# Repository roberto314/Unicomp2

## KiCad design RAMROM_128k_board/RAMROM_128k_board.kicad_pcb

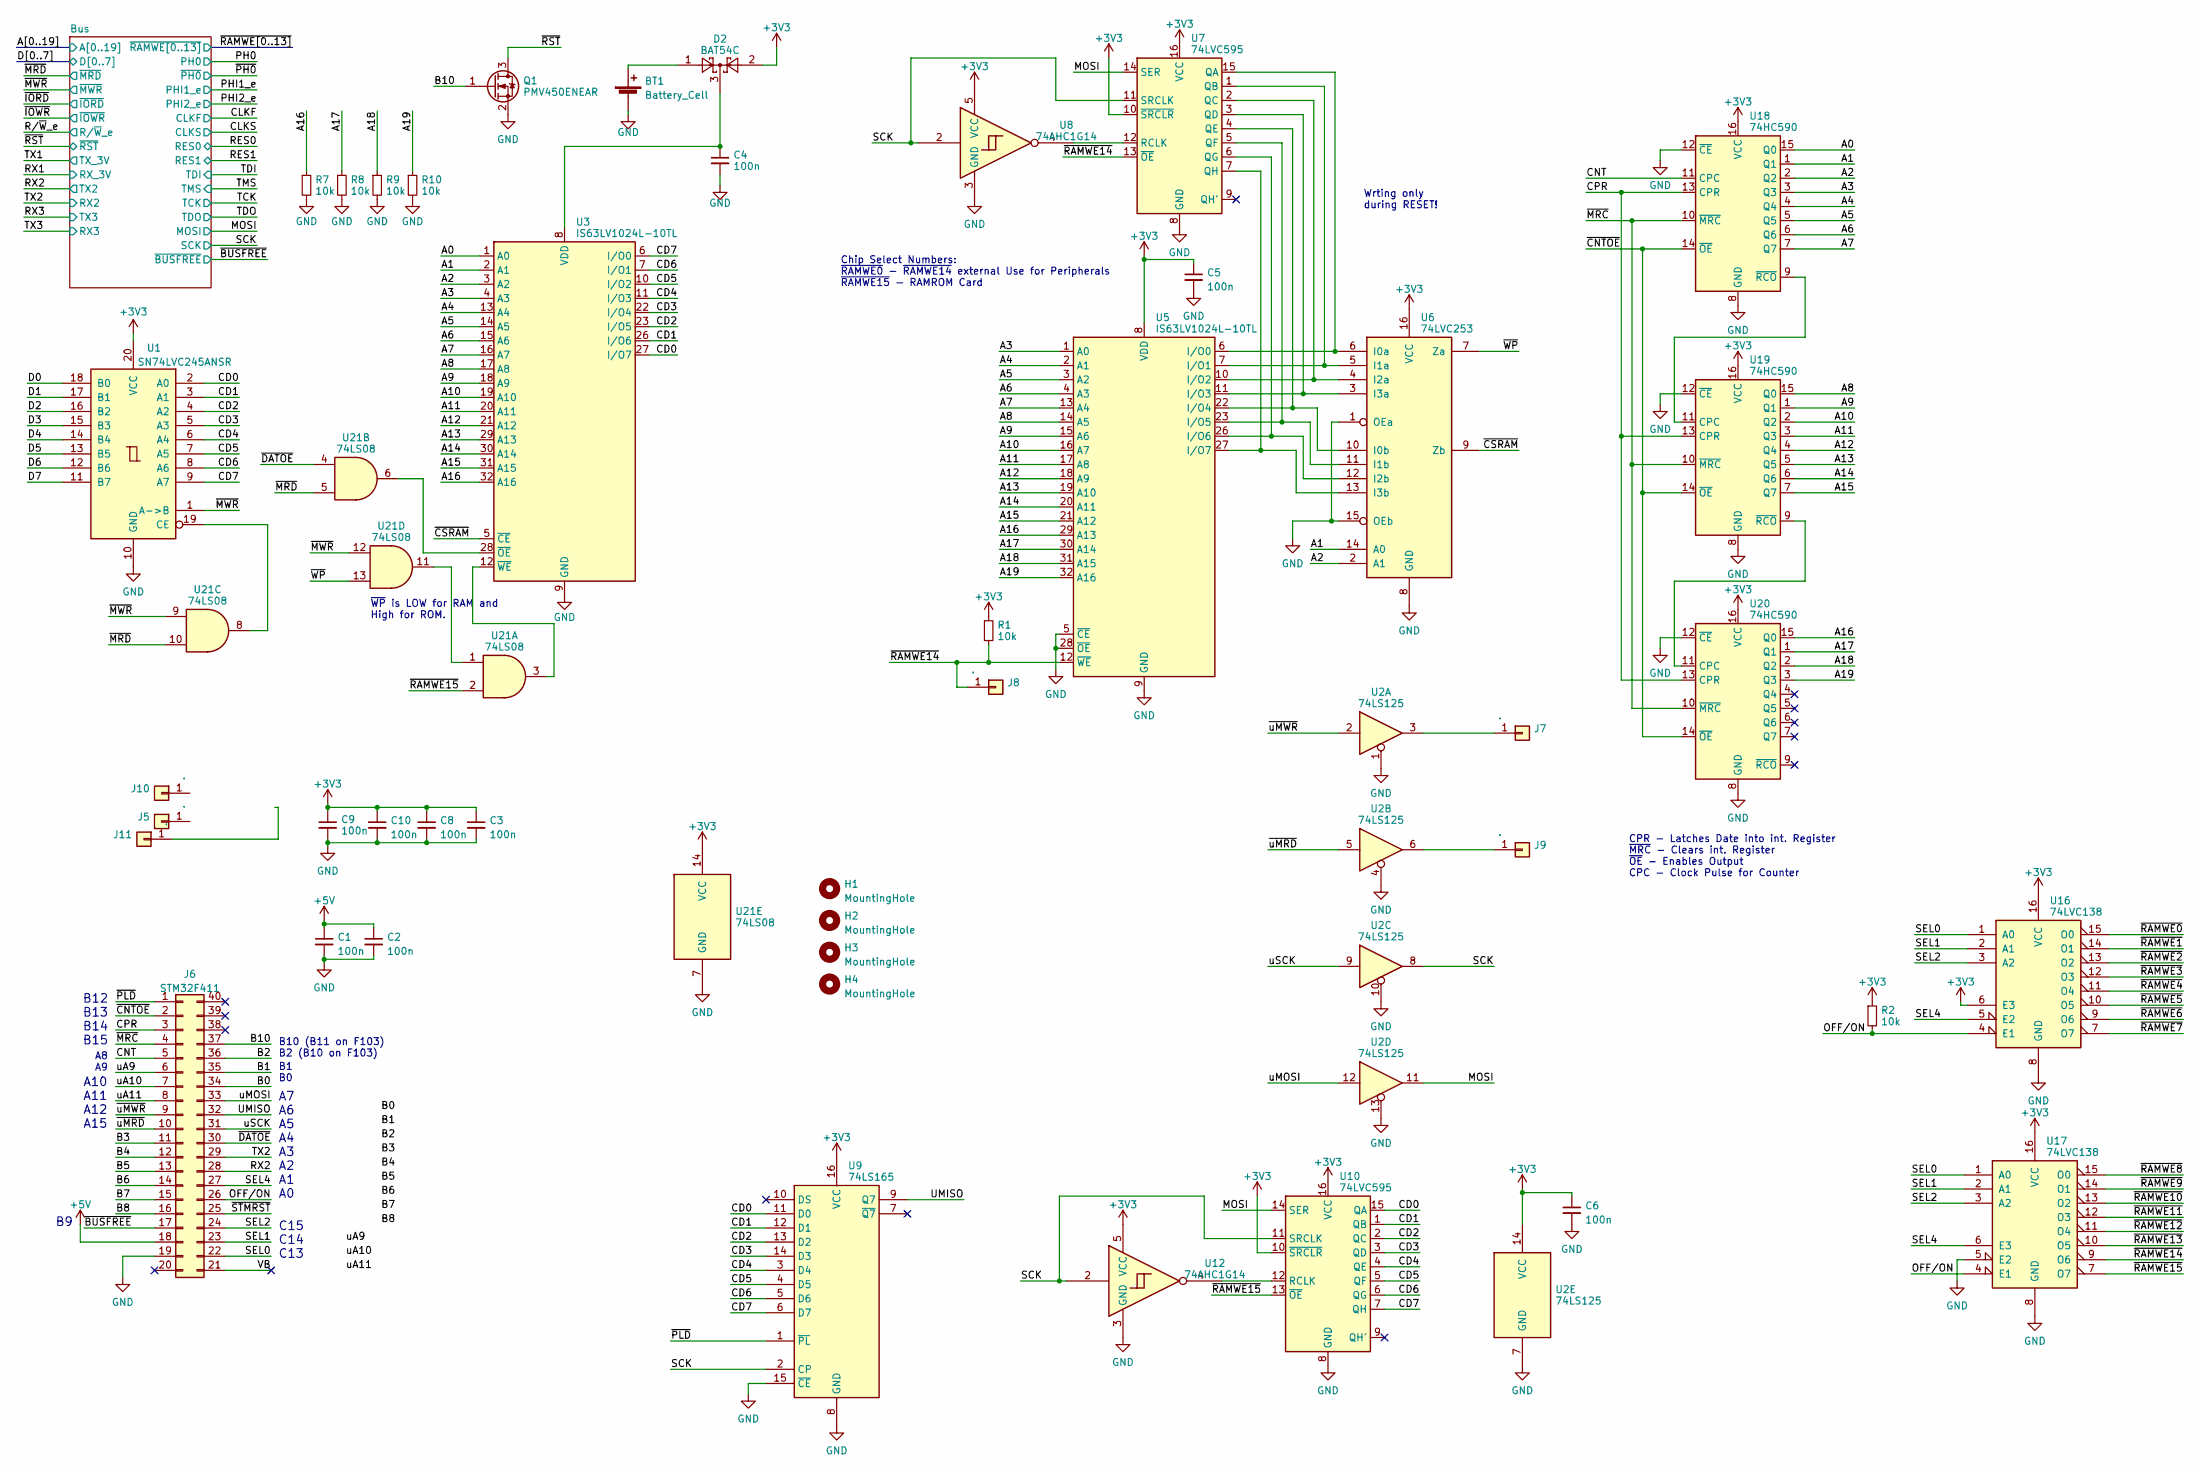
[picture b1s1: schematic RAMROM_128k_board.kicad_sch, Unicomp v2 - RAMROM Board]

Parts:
BT1: Battery_Cell; BatteryHolder_Keystone_103_1x20mm
C1, C2, C3, C4, C5, C6, C8, C9, C10: 100n; C_1206_3216Metric
D2: BAT54C; SOT-23
H1, H2, H3, H4: MountingHole; MountingHole_3.2mm_M3
J5, J7, J8, J9, J10, J11: .; PinHeader_1x01_P2.00mm_Vertical
J6: STM32F411; DIP-40_W15.24mm_Socket_LongPads
Q1: PMV450ENEAR; SOT-23
R1, R2, R7, R8, R9, R10: 10k; R_1206_3216Metric_Pad1.30x1.75mm_HandSolder
U1: SN74LVC245ANSR; SO-20_5.3x12.6mm_P1.27mm
U2: 74LS125; SOIC-14_3.9x8.7mm_P1.27mm
U3, U5: IS63LV1024L-10TL; TSOP-II-32_21.0x10.2mm_P1.27mm
U6: 74LVC253; SO-16_3.9x9.9mm_P1.27mm
U7, U10: 74LVC595; SO-16_3.9x9.9mm_P1.27mm
U8, U12: 74AHC1G14; SOT-23-5
U9: 74LS165; SOIC-16_3.9x9.9mm_P1.27mm
U16, U17: 74LVC138; SOIC-16_3.9x9.9mm_P1.27mm
U18, U19, U20: 74HC590; SOIC-16_3.9x9.9mm_P1.27mm
U21: 74LS08; SOIC-14_3.9x8.7mm_P1.27mm

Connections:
+3V3: C3.1, C5.1, C6.1, C8.1, C9.1, C10.1, D2.2, R1.1, R2.1, U1.20 (VCC), U2.14 (VCC), U5.8 (VDD), U5.24 (VDD), U6.16 (VCC), U7.10 (~SRCLR), U7.16 (VCC), U8.5 (VCC), U9.16 (VCC), U10.10 (~SRCLR), U10.16 (VCC), U12.5 (VCC), U16.6 (E3), U16.16 (VCC), U17.16 (VCC), U18.16 (VCC), U19.16 (VCC), U20.16 (VCC), U21.14 (VCC); also elsewhere on the board
+5V: C1.1, C2.1, J6.18; also elsewhere on the board
/A0: U3.1 (A0), U18.15 (Q0); also elsewhere on the board
/A1: U3.2 (A1), U6.14 (A0), U18.1 (Q1); also elsewhere on the board
/A2: U3.3 (A2), U6.2 (A1), U18.2 (Q2); also elsewhere on the board
/A3: U3.4 (A3), U5.1 (A0), U18.3 (Q3); also elsewhere on the board
/A4: U3.13 (A4), U5.2 (A1), U18.4 (Q4); also elsewhere on the board
/A5: U3.14 (A5), U5.3 (A2), U18.5 (Q5); also elsewhere on the board
/A6: U3.15 (A6), U5.4 (A3), U18.6 (Q6); also elsewhere on the board
/A7: U3.16 (A7), U5.13 (A4), U18.7 (Q7); also elsewhere on the board
/A8: U3.17 (A8), U5.14 (A5), U19.15 (Q0); also elsewhere on the board
/A9: U3.18 (A9), U5.15 (A6), U19.1 (Q1); also elsewhere on the board
/A10: U3.19 (A10), U5.16 (A7), U19.2 (Q2); also elsewhere on the board
/A11: U3.20 (A11), U5.17 (A8), U19.3 (Q3); also elsewhere on the board
/A12: U3.21 (A12), U5.18 (A9), U19.4 (Q4); also elsewhere on the board
/A13: U3.29 (A13), U5.19 (A10), U19.5 (Q5); also elsewhere on the board
/A14: U3.30 (A14), U5.20 (A11), U19.6 (Q6); also elsewhere on the board
/A15: U3.31 (A15), U5.21 (A12), U19.7 (Q7); also elsewhere on the board
/A16: R7.1, U3.32 (A16), U5.29 (A13), U20.15 (Q0); also elsewhere on the board
/A17: R8.1, U5.30 (A14), U20.1 (Q1); also elsewhere on the board
/A18: R9.1, U5.31 (A15), U20.2 (Q2); also elsewhere on the board
/A19: R10.1, U5.32 (A16), U20.3 (Q3); also elsewhere on the board
/B0: J6.34
/B1: J6.35
/B2: J6.36
/B3: J6.11
/B4: J6.12
/B5: J6.13
/B6: J6.14
/B7: J6.15
/B8: J6.16
/B10: J6.37, Q1.1 (G)
/CD0: U1.2 (A0), U3.27 (I/O7), U9.11 (D0), U10.15 (QA)
/CD1: U1.3 (A1), U3.26 (I/O6), U9.12 (D1), U10.1 (QB)
/CD2: U1.4 (A2), U3.23 (I/O5), U9.13 (D2), U10.2 (QC)
/CD3: U1.5 (A3), U3.22 (I/O4), U9.14 (D3), U10.3 (QD)
/CD4: U1.6 (A4), U3.11 (I/O3), U9.3 (D4), U10.4 (QE)
/CD5: U1.7 (A5), U3.10 (I/O2), U9.4 (D5), U10.5 (QF)
/CD6: U1.8 (A6), U3.7 (I/O1), U9.5 (D6), U10.6 (QG)
/CD7: U1.9 (A7), U3.6 (I/O0), U9.6 (D7), U10.7 (QH)
/CNT: J6.5, U18.11 (CPC)
/CPR: J6.3, U18.13 (CPR), U19.13 (CPR), U20.13 (CPR)
/D0: U1.18 (B0); also elsewhere on the board
/D1: U1.17 (B1); also elsewhere on the board
/D2: U1.16 (B2); also elsewhere on the board
/D3: U1.15 (B3); also elsewhere on the board
/D4: U1.14 (B4); also elsewhere on the board
/D5: U1.13 (B5); also elsewhere on the board
/D6: U1.12 (B6); also elsewhere on the board
/D7: U1.11 (B7); also elsewhere on the board
/MOSI: U2.11, U7.14 (SER), U10.14 (SER); also elsewhere on the board
/OFF/ON: J6.26, R2.2, U16.4 (E1), U17.4 (E1)
/RX2: J6.28; also elsewhere on the board
/SCK: U2.8, U7.11 (SRCLK), U8.2, U9.2 (CP), U10.11 (SRCLK), U12.2; also elsewhere on the board
/SEL0: J6.22, U16.1 (A0), U17.1 (A0)
/SEL1: J6.23, U16.2 (A1), U17.2 (A1)
/SEL2: J6.24, U16.3 (A2), U17.3 (A2)
/SEL4: J6.27, U16.5 (E2), U17.6 (E3)
/TX2: J6.29; also elsewhere on the board
/UMISO: J6.32, U9.9 (Q7)
/VB: J6.21
/uA9: J6.6
/uA10: J6.7
/uA11: J6.8
/uMOSI: J6.33, U2.12
/uSCK: J6.31, U2.9
/~BUSFREE: J6.17; also elsewhere on the board
/~CNTOE: J6.2, U18.14 (~OE), U19.14 (~OE), U20.14 (~OE)
/~CSRAM: U3.5 (~CE), U6.9 (Zb)
/~DATOE: J6.30, U21.4
/~MRC: J6.4, U18.10 (~MRC), U19.10 (~MRC), U20.10 (~MRC)
/~MRD: U21.5, U21.10; also elsewhere on the board
/~MWR: U1.1 (A->B), U21.9, U21.12; also elsewhere on the board
/~PLD: J6.1, U9.1 (~PL)
/~RAMWE0: U16.15 (O0); also elsewhere on the board
/~RAMWE1: U16.14 (O1); also elsewhere on the board
/~RAMWE2: U16.13 (O2); also elsewhere on the board
/~RAMWE3: U16.12 (O3); also elsewhere on the board
/~RAMWE4: U16.11 (O4); also elsewhere on the board
/~RAMWE5: U16.10 (O5); also elsewhere on the board
/~RAMWE6: U16.9 (O6); also elsewhere on the board
/~RAMWE7: U16.7 (O7); also elsewhere on the board
/~RAMWE8: U17.15 (O0); also elsewhere on the board
/~RAMWE9: U17.14 (O1); also elsewhere on the board
/~RAMWE10: U17.13 (O2); also elsewhere on the board
/~RAMWE11: U17.12 (O3); also elsewhere on the board
/~RAMWE12: U17.11 (O4); also elsewhere on the board
/~RAMWE13: U17.10 (O5); also elsewhere on the board
/~RAMWE14: J8.1, R1.2, U5.12 (~WE), U7.13 (~OE), U17.9 (O6)
/~RAMWE15: U10.13 (~OE), U17.7 (O7), U21.2
/~RST: Q1.3 (D); also elsewhere on the board
/~STMRST: J6.25
/~WP: U6.7 (Za), U21.13
/~uMRD: J6.10, U2.5
/~uMWR: J6.9, U2.2
GND: BT1.2 (-), C1.2, C2.2, C3.2, C4.2, C5.2, C6.2, C8.2, C9.2, C10.2, J6.19, Q1.2 (S), R7.2, R8.2, R9.2, R10.2, U1.10 (GND), U2.1, U2.4, U2.7 (GND), U2.10, U2.13, U3.9 (GND), U3.25 (GND), U5.5 (~CE), U5.9 (GND), U5.25 (GND), U5.28 (~OE), U6.1 (OEa), U6.8 (GND), U6.15 (OEb), U7.8 (GND), U8.3 (GND), U9.8 (GND), U9.15 (~CE), U10.8 (GND), U12.3 (GND), U16.8 (GND), U17.5 (E2), U17.8 (GND), U18.8 (GND), U18.12 (~CE), U19.8 (GND), U19.12 (~CE), U20.8 (GND), U20.12 (~CE), U21.7 (GND); also elsewhere on the board
unnamed: BT1.1 (+), D2.1
unnamed: C4.1, D2.3, U3.8 (VDD), U3.24 (VDD)
unnamed: J7.1, U2.3
unnamed: J9.1, U2.6
unnamed: U1.19 (CE), U21.8
unnamed: U3.28 (~OE), U21.6
unnamed: U3.12 (~WE), U21.3
unnamed: U5.6 (I/O0), U6.6 (I0a), U7.15 (QA)
unnamed: U5.7 (I/O1), U6.5 (I1a), U7.1 (QB)
unnamed: U5.10 (I/O2), U6.4 (I2a), U7.2 (QC)
unnamed: U5.11 (I/O3), U6.3 (I3a), U7.3 (QD)
unnamed: U5.22 (I/O4), U6.10 (I0b), U7.4 (QE)
unnamed: U5.23 (I/O5), U6.11 (I1b), U7.5 (QF)
unnamed: U5.26 (I/O6), U6.12 (I2b), U7.6 (QG)
unnamed: U5.27 (I/O7), U6.13 (I3b), U7.7 (QH)
unnamed: U7.12 (RCLK), U8.4
unnamed: U10.12 (RCLK), U12.4
unnamed: U18.9 (~RCO), U19.11 (CPC)
unnamed: U19.9 (~RCO), U20.11 (CPC)
unnamed: U21.1, U21.11

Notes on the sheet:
B1 B0
A10 A11 A12 A15
CPR - Latches Date into int. Register ~{MRC} - Clears int. Register ~{OE} - Enables Output CPC - Clock Pulse for Counter
Wrting only during RESET!
A8 A9
B10 (B11 on F103) B2 (B10 on F103)
~{WP} is LOW for RAM and High for ROM.
A7 A6 A5 A4 A3 A2 A1 A0
B12 B13 B14 B15
C15 C14 C13
Chip Select Numbers: ~{RAMWE0} - ~{RAMWE14} external Use for Peripherals ~{RAMWE15} - RAMROM Card

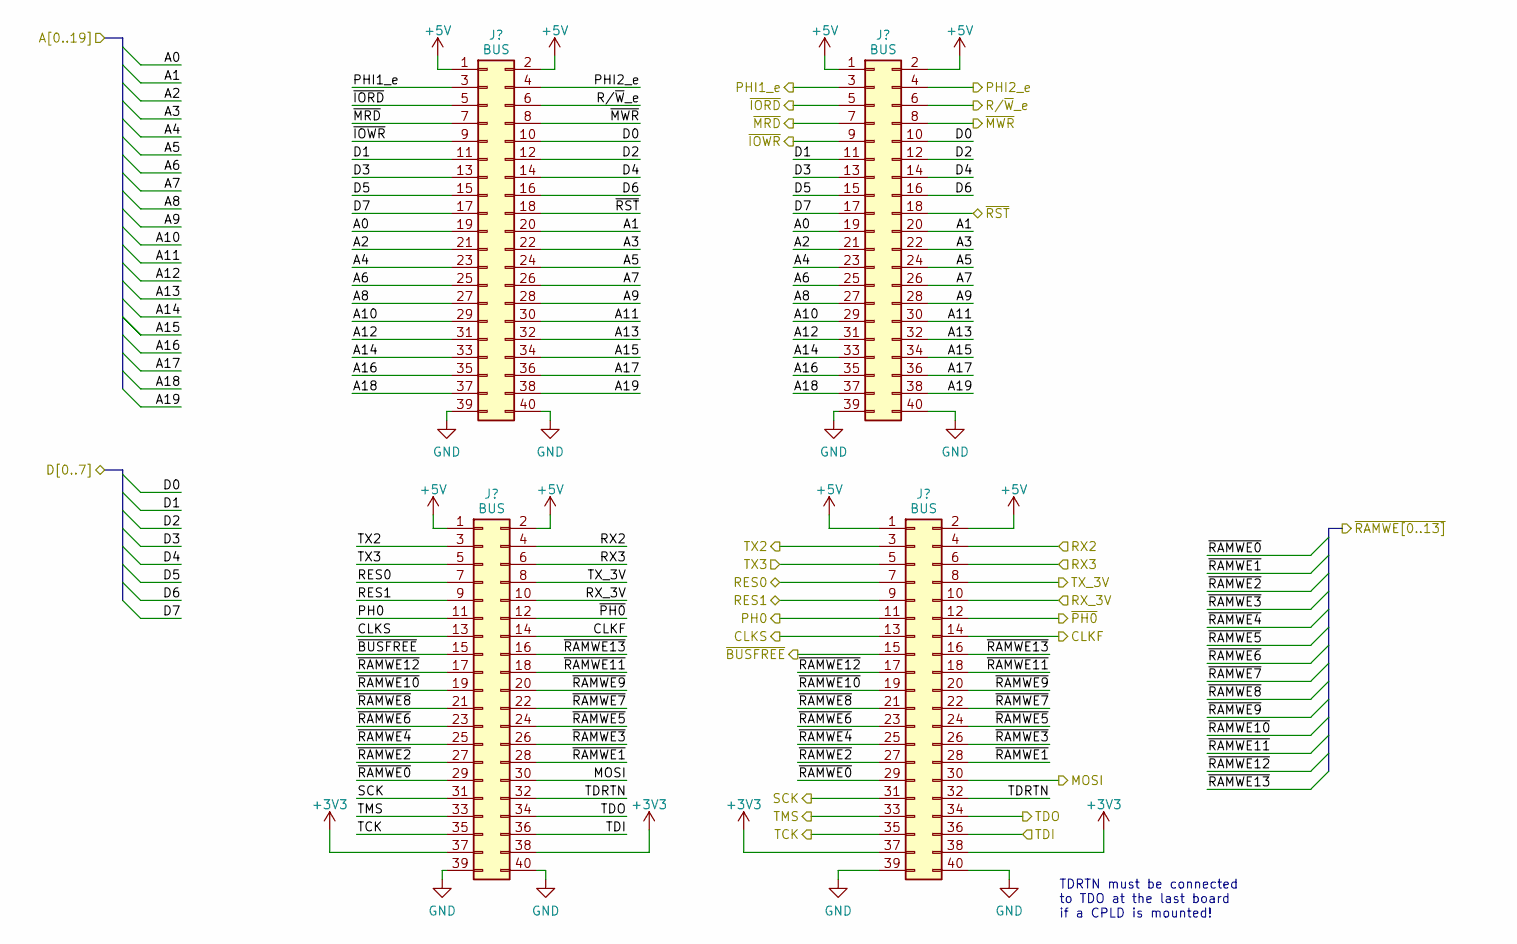
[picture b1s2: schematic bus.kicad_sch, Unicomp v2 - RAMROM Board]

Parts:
J1, J2, J3, J4: BUS; PinSocket_2x20_P2.54mm_Vertical

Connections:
+3V3: J2.37, J2.38, J4.37, J4.38; also elsewhere on the board
+5V: J1.1, J1.2, J2.1, J2.2, J3.1, J3.2, J4.1, J4.2; also elsewhere on the board
/A0: J1.19, J3.19; also elsewhere on the board
/A1: J1.20, J3.20; also elsewhere on the board
/A2: J1.21, J3.21; also elsewhere on the board
/A3: J1.22, J3.22; also elsewhere on the board
/A4: J1.23, J3.23; also elsewhere on the board
/A5: J1.24, J3.24; also elsewhere on the board
/A6: J1.25, J3.25; also elsewhere on the board
/A7: J1.26, J3.26; also elsewhere on the board
/A8: J1.27, J3.27; also elsewhere on the board
/A9: J1.28, J3.28; also elsewhere on the board
/A10: J1.29, J3.29; also elsewhere on the board
/A11: J1.30, J3.30; also elsewhere on the board
/A12: J1.31, J3.31; also elsewhere on the board
/A13: J1.32, J3.32; also elsewhere on the board
/A14: J1.33, J3.33; also elsewhere on the board
/A15: J1.34, J3.34; also elsewhere on the board
/A16: J1.35, J3.35; also elsewhere on the board
/A17: J1.36, J3.36; also elsewhere on the board
/A18: J1.37, J3.37; also elsewhere on the board
/A19: J1.38, J3.38; also elsewhere on the board
/Bus/TDRTN: J2.32, J4.32
/CLKF: J2.14, J4.14
/CLKS: J2.13, J4.13
/D0: J1.10, J3.10; also elsewhere on the board
/D1: J1.11, J3.11; also elsewhere on the board
/D2: J1.12, J3.12; also elsewhere on the board
/D3: J1.13, J3.13; also elsewhere on the board
/D4: J1.14, J3.14; also elsewhere on the board
/D5: J1.15, J3.15; also elsewhere on the board
/D6: J1.16, J3.16; also elsewhere on the board
/D7: J1.17, J3.17; also elsewhere on the board
/MOSI: J2.30, J4.30; also elsewhere on the board
/PH0: J2.11, J4.11
/PHI1_e: J1.3, J3.3
/PHI2_e: J1.4, J3.4
/RES0: J2.7, J4.7
/RES1: J2.9, J4.9
/RX1: J2.10, J4.10
/RX2: J2.3, J4.3; also elsewhere on the board
/RX3: J2.5, J4.5
/R/~W_e: J1.6, J3.6
/SCK: J2.31, J4.31; also elsewhere on the board
/TCK: J2.35, J4.35
/TDI: J2.36, J4.36
/TDO: J2.34, J4.34
/TMS: J2.33, J4.33
/TX1: J2.8, J4.8
/TX2: J2.4, J4.4; also elsewhere on the board
/TX3: J2.6, J4.6
/~BUSFREE: J2.15, J4.15; also elsewhere on the board
/~IORD: J1.5, J3.5
/~IOWR: J1.9, J3.9
/~MRD: J1.7, J3.7; also elsewhere on the board
/~MWR: J1.8, J3.8; also elsewhere on the board
/~PH0: J2.12, J4.12
/~RAMWE0: J2.29, J4.29; also elsewhere on the board
/~RAMWE1: J2.28, J4.28; also elsewhere on the board
/~RAMWE2: J2.27, J4.27; also elsewhere on the board
/~RAMWE3: J2.26, J4.26; also elsewhere on the board
/~RAMWE4: J2.25, J4.25; also elsewhere on the board
/~RAMWE5: J2.24, J4.24; also elsewhere on the board
/~RAMWE6: J2.23, J4.23; also elsewhere on the board
/~RAMWE7: J2.22, J4.22; also elsewhere on the board
/~RAMWE8: J2.21, J4.21; also elsewhere on the board
/~RAMWE9: J2.20, J4.20; also elsewhere on the board
/~RAMWE10: J2.19, J4.19; also elsewhere on the board
/~RAMWE11: J2.18, J4.18; also elsewhere on the board
/~RAMWE12: J2.17, J4.17; also elsewhere on the board
/~RAMWE13: J2.16, J4.16; also elsewhere on the board
/~RST: J1.18, J3.18; also elsewhere on the board
GND: J1.39, J1.40, J2.39, J2.40, J3.39, J3.40, J4.39, J4.40; also elsewhere on the board

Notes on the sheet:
TDRTN must be connected to TDO at the last board if a CPLD is mounted!

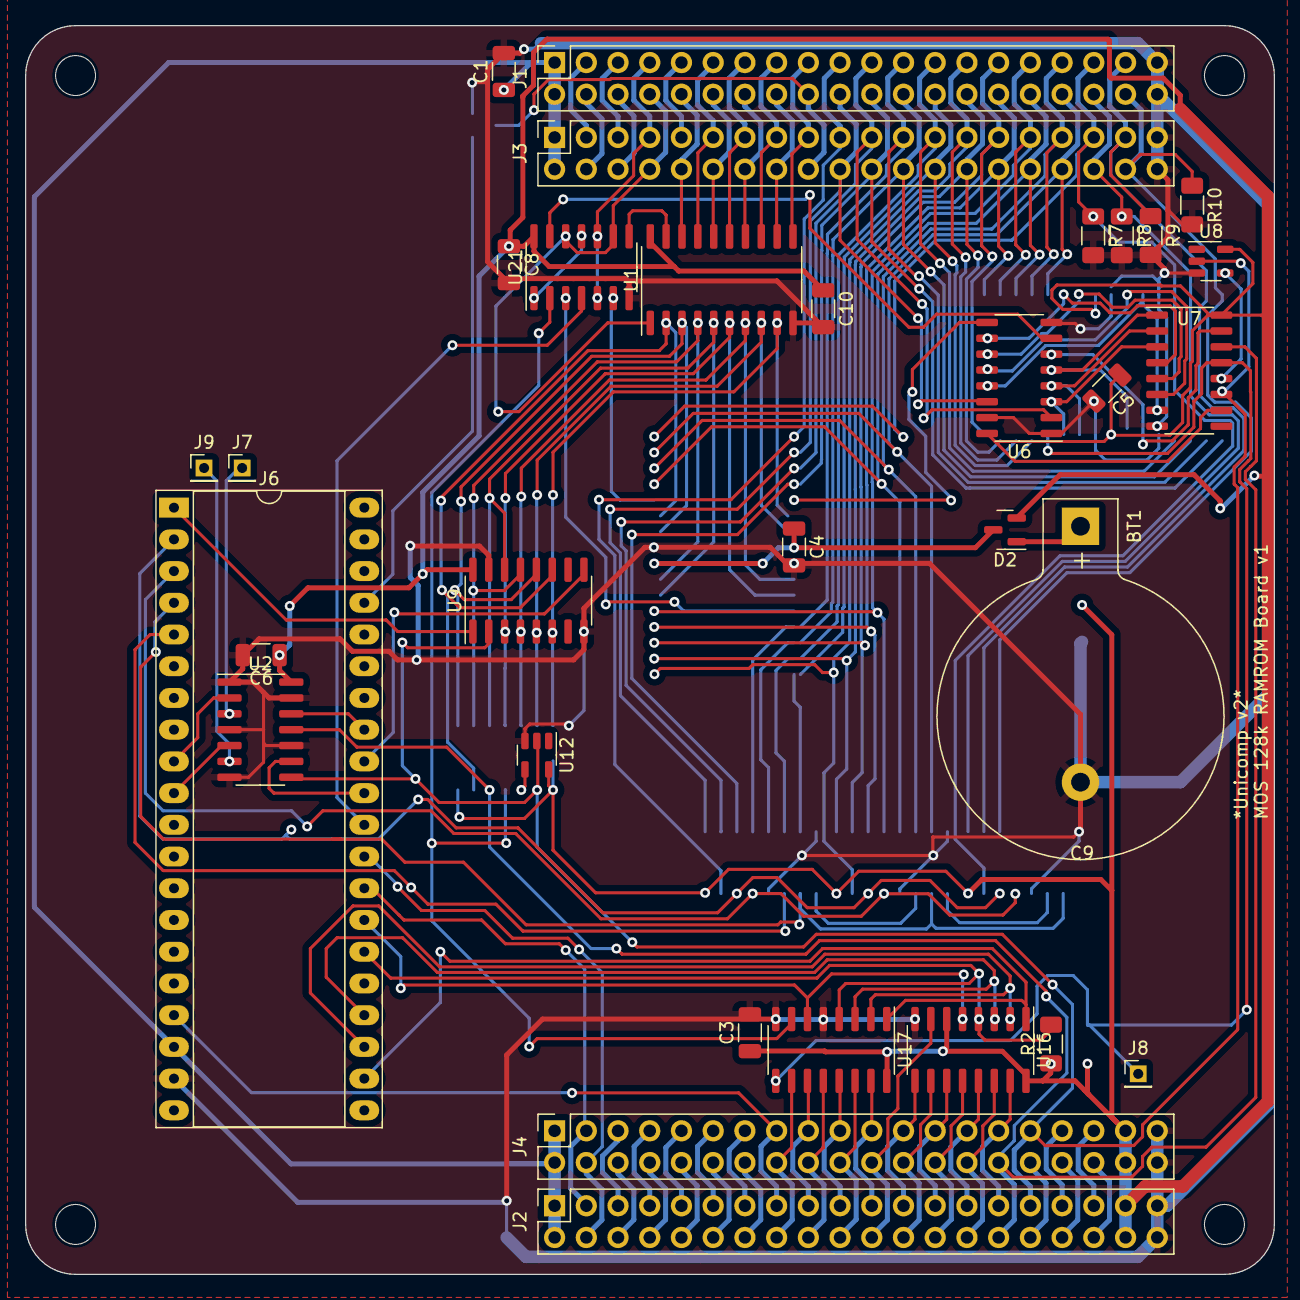
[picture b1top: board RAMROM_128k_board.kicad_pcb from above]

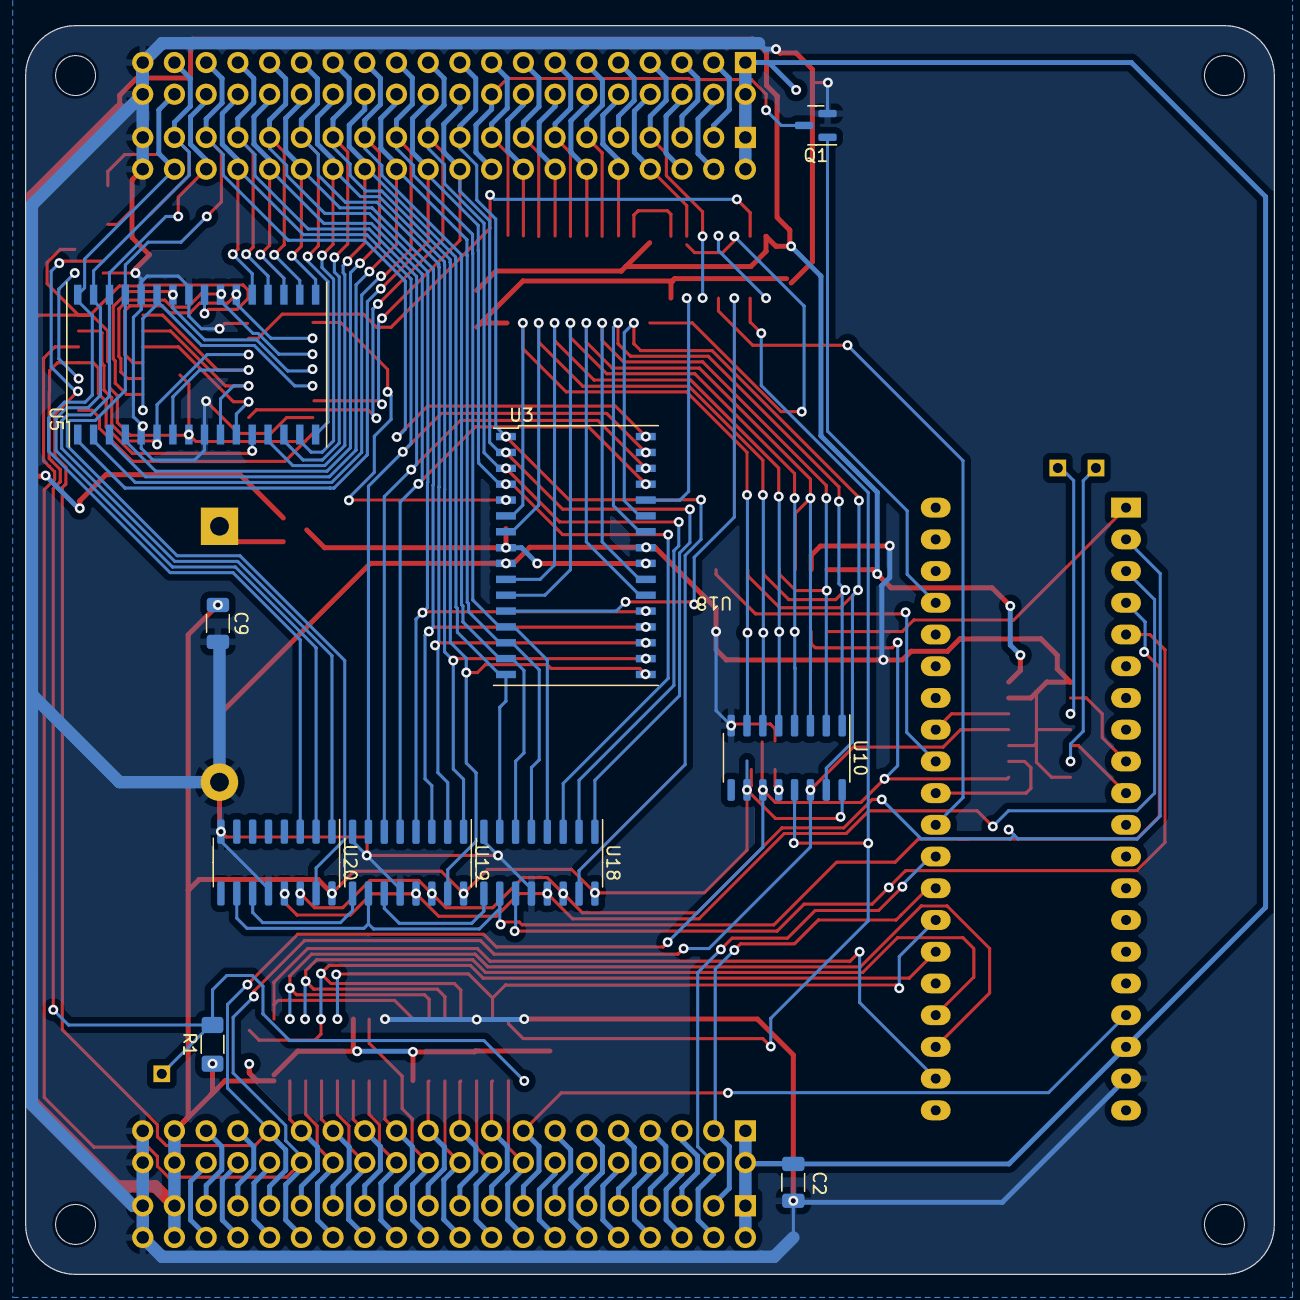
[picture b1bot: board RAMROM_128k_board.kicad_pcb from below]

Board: 2 copper layers, 100.0 x 100.0 mm, 46 parts (10 on the bottom side), 122 nets.

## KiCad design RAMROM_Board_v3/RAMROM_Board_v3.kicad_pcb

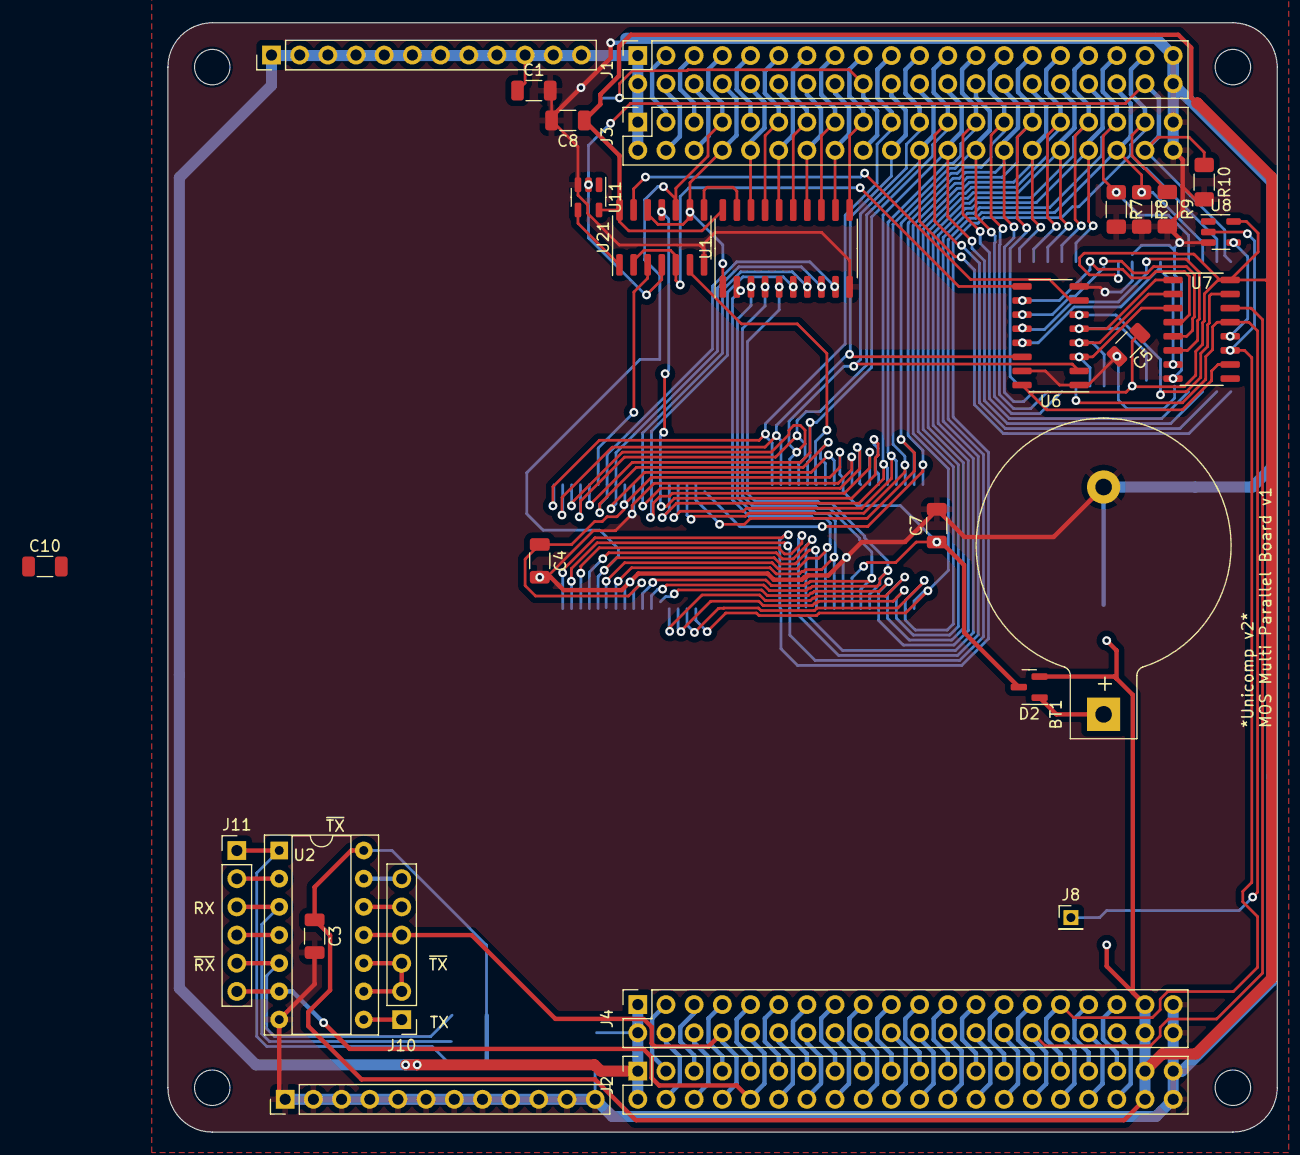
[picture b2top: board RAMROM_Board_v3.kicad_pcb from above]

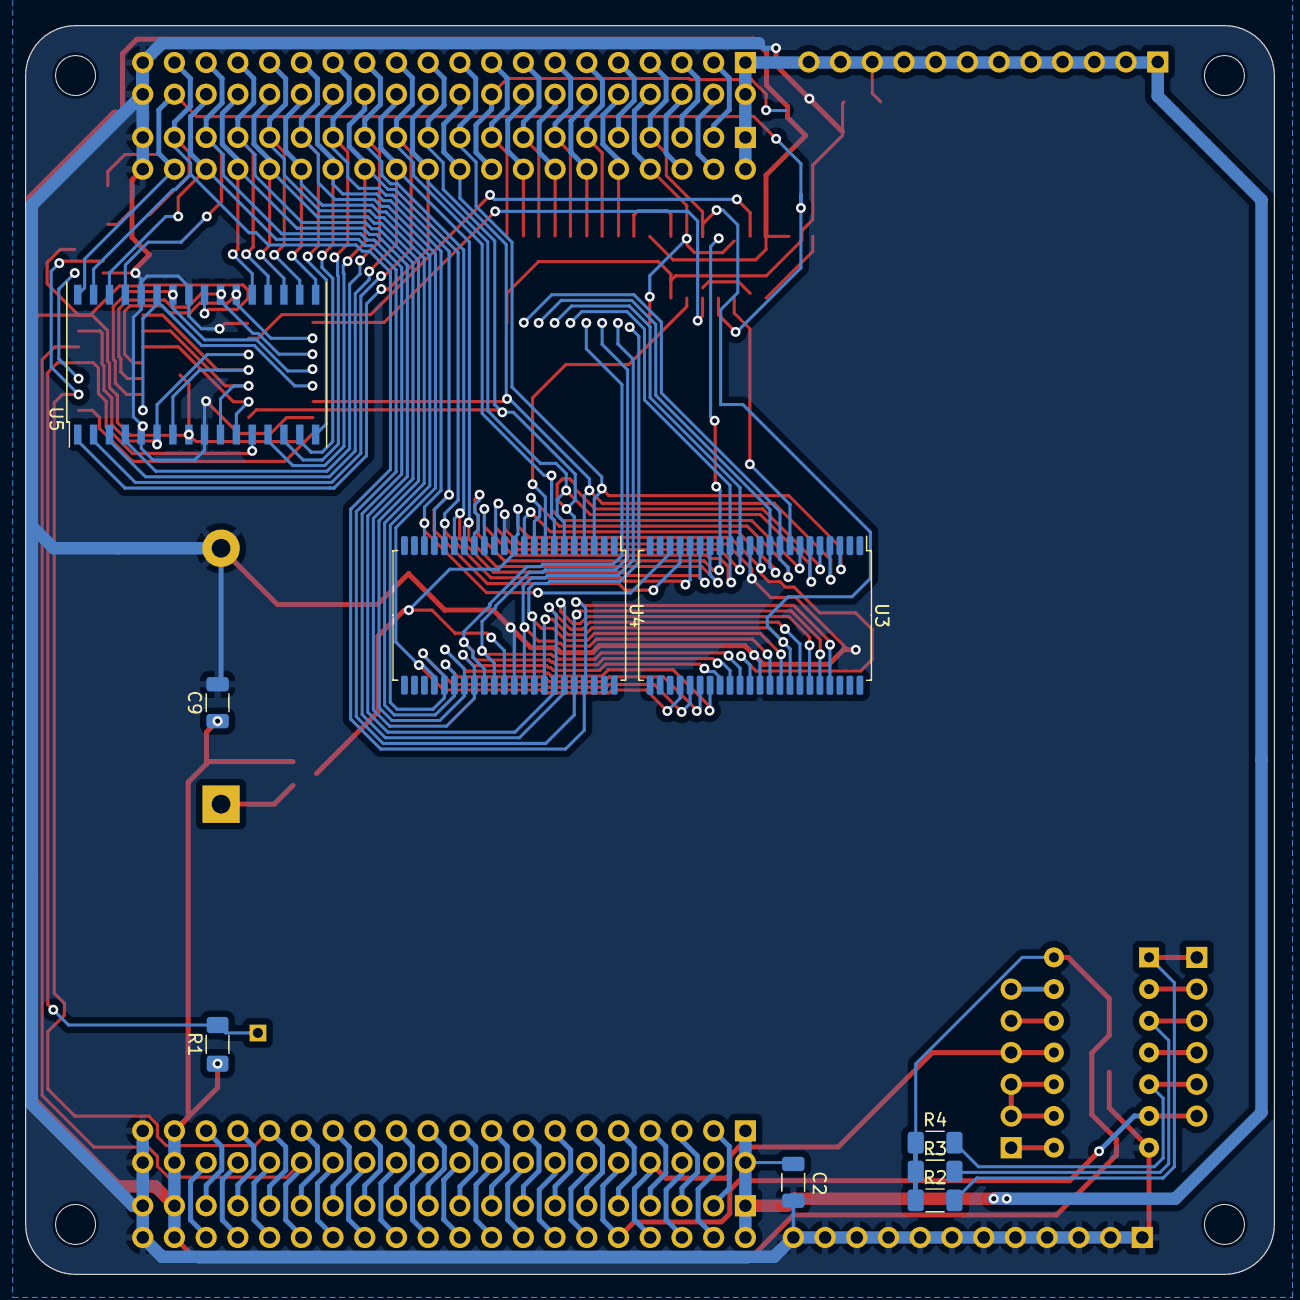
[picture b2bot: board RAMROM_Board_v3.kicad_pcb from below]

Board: 2 copper layers, 100.0 x 100.0 mm, 42 parts (9 on the bottom side), 109 nets.

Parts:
BT1: Battery_Cell; BatteryHolder_Keystone_103_1x20mm
C1, C2, C3, C4, C5, C7, C8, C9, C10: 100n; C_1206_3216Metric
D2: BAT54C; SOT-23
H1, H2, H3, H4: MountingHole; MountingHole_3.2mm_M3
J1, J2, J3, J4: BUS; PinSocket_2x20_P2.54mm_Vertical
J8: .; PinHeader_1x01_P2.00mm_Vertical
J10, J11: .; PinHeader_1x06_P2.54mm_Vertical
J20, J21: Conn_01x12; PinHeader_1x12_P2.54mm_Vertical
R1, R7, R8, R9, R10: 10k; R_1206_3216Metric_Pad1.30x1.75mm_HandSolder
R2, R3, R4: 1k; R_1206_3216Metric_Pad1.30x1.75mm_HandSolder
U1: SN74LVC245ANSR; SO-20_5.3x12.6mm_P1.27mm
U2: 74HC14; DIP-14_W7.62mm_Socket
U3, U4: IS61C5128AL-10TLI; TSOP-II-44_10.16x18.41mm_P0.8mm
U5: IS63WV1288DBLL-10xLI; TSOP-II-32_21.0x10.2mm_P1.27mm
U6: 74LVC253; SO-16_3.9x9.9mm_P1.27mm
U7: 74LVC595; SO-16_3.9x9.9mm_P1.27mm
U8, U11: 74AHC1G14; SOT-23-5
U21: 74LS08; SOIC-14_3.9x8.7mm_P1.27mm

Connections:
+3V3: C3.1, C5.1, C8.1, C9.1, C10.1, D2.2, J2.37, J2.38, J4.37, J4.38, R1.1, R2.1, R3.1, R4.1, U1.20 (VCC), U2.14 (VCC), U5.8 (VDD), U5.24 (VDD), U6.16 (VCC), U7.10 (~SRCLR), U7.16 (VCC), U8.5 (VCC), U11.5 (VCC), U21.14 (VCC)
+5V: C1.1, C2.1, J1.1, J1.2, J2.1, J2.2, J3.1, J3.2, J4.1, J4.2, J21.1, J21.2, J21.3, J21.4, J21.5, J21.6, J21.7, J21.8, J21.9, J21.10, J21.11, J21.12
/A0: J1.19, J3.19, U3.3 (A0), U4.3 (A0)
/A1: J1.20, J3.20, U3.4 (A1), U4.4 (A1), U6.14 (A0)
/A2: J1.21, J3.21, U3.5 (A2), U4.5 (A2), U6.2 (A1)
/A3: J1.22, J3.22, U3.6 (A3), U4.6 (A3), U5.1 (A0)
/A4: J1.23, J3.23, U3.7 (A4), U4.7 (A4), U5.2 (A1)
/A5: J1.24, J3.24, U3.16 (A5), U4.16 (A5), U5.3 (A2)
/A6: J1.25, J3.25, U3.17 (A6), U4.17 (A6), U5.4 (A3)
/A7: J1.26, J3.26, U3.18 (A7), U4.18 (A7), U5.13 (A4)
/A8: J1.27, J3.27, U3.19 (A8), U4.19 (A8), U5.14 (A5)
/A9: J1.28, J3.28, U3.20 (A9), U4.20 (A9), U5.15 (A6)
/A10: J1.29, J3.29, U3.26 (A10), U4.26 (A10), U5.16 (A7)
/A11: J1.30, J3.30, U3.27 (A11), U4.27 (A11), U5.17 (A8)
/A12: J1.31, J3.31, U3.28 (A12), U4.28 (A12), U5.18 (A9)
/A13: J1.32, J3.32, U3.29 (A13), U4.29 (A13), U5.19 (A10)
/A14: J1.33, J3.33, U3.30 (A14), U4.30 (A14), U5.20 (A11)
/A15: J1.34, J3.34, U3.38 (A15), U4.38 (A15), U5.21 (A12)
/A16: J1.35, J3.35, R7.1, U3.39 (A16), U4.39 (A16), U5.29 (A13)
/A17: J1.36, J3.36, R8.1, U3.40 (A17), U4.40 (A17), U5.30 (A14)
/A18: J1.37, J3.37, R9.1, U3.41 (A18), U4.41 (A18), U5.31 (A15)
/A19: J1.38, J3.38, R10.1, U5.32 (A16), U11.2, U21.4
/Bus/TDRTN: J2.32, J4.32
/CB2: J10.6, U2.13
/CD0: U1.2 (A0), U3.36 (I/O7), U4.36 (I/O7)
/CD1: U1.3 (A1), U3.35 (I/O6), U4.35 (I/O6)
/CD2: U1.4 (A2), U3.32 (I/O5), U4.32 (I/O5)
/CD3: U1.5 (A3), U3.31 (I/O4), U4.31 (I/O4)
/CD4: U1.6 (A4), U3.14 (I/O3), U4.14 (I/O3)
/CD5: U1.7 (A5), U3.13 (I/O2), U4.13 (I/O2)
/CD6: U1.8 (A6), U3.10 (I/O1), U4.10 (I/O1)
/CD7: U1.9 (A7), U3.9 (I/O0), U4.9 (I/O0)
/CLKF: J2.14, J4.14
/CLKS: J2.13, J4.13
/D0: J1.10, J3.10, U1.18 (B0)
/D1: J1.11, J3.11, U1.17 (B1)
/D2: J1.12, J3.12, U1.16 (B2)
/D3: J1.13, J3.13, U1.15 (B3)
/D4: J1.14, J3.14, U1.14 (B4)
/D5: J1.15, J3.15, U1.13 (B5)
/D6: J1.16, J3.16, U1.12 (B6)
/D7: J1.17, J3.17, U1.11 (B7)
/MOSI: J2.30, J4.30, U7.14 (SER)
/PH0: J2.11, J4.11
/PHI1_e: J1.3, J3.3
/PHI2_e: J1.4, J3.4
/RES0: J2.7, J4.7
/RES1: J2.9, J4.9
/RX1: J2.10, J4.10, J11.6, U2.6
/RX1#: J11.3, R3.2, U2.3
/RX2: J2.4, J4.4
/RX3: J2.6, J4.6
/R/~W_e: J1.6, J3.6
/SCK: J2.31, J4.31, U7.11 (SRCLK), U8.2
/TCK: J2.35, J4.35
/TDI: J2.36, J4.36
/TDO: J2.34, J4.34
/TMS: J2.33, J4.33
/TX1: J2.8, J4.8, J10.4, U2.11
/TX1#: J10.1, U2.8
/TX2: J2.3, J4.3
/TX3: J2.5, J4.5
/~CSRAM: U6.9 (Zb), U21.2, U21.5
/~IORD: J1.5, J3.5
/~IOWR: J1.9, J3.9
/~MRD: J1.7, J3.7, U3.37 (~OE), U4.37 (~OE), U21.10
/~MWR: J1.8, J3.8, U1.1 (A->B), U21.9, U21.12
/~PH0: J2.12, J4.12
/~RAMWE0: J2.29, J4.29
/~RAMWE1: J2.28, J4.28
/~RAMWE2: J2.27, J4.27
/~RAMWE3: J2.26, J4.26
/~RAMWE4: J2.25, J4.25
/~RAMWE5: J2.24, J4.24
/~RAMWE6: J2.23, J4.23
/~RAMWE7: J2.22, J4.22
/~RAMWE8: J2.21, J4.21
/~RAMWE9: J2.20, J4.20
/~RAMWE10: J2.19, J4.19
/~RAMWE11: J2.18, J4.18
/~RAMWE12: J2.17, J4.17
/~RAMWE13: J2.16, J4.16
/~RAMWE14: J2.15, J4.15
/~RAMWE15: J8.1, R1.2, U5.12 (~WE), U7.13 (~OE)
/~RST: J1.18, J3.18
/~RX1: J11.4, U2.4
/~RX1': J11.5, R4.2, U2.5
/~TX1: J10.2, J10.3, U2.9, U2.10
/~WP: U6.7 (Za), U21.13
GND: BT1.2 (-), C1.2, C2.2, C3.2, C4.2, C5.2, C7.2, C8.2, C9.2, C10.2, J1.39, J1.40, J2.39, J2.40, J3.39, J3.40, J4.39, J4.40, J20.1, J20.2, J20.3, J20.4, J20.5, J20.6, J20.7, J20.8, J20.9, J20.10, J20.11, J20.12, R7.2, R8.2, R9.2, R10.2, U1.10 (GND), U2.7 (GND), U3.12 (GND), U3.34 (GND), U4.12 (GND), U4.34 (GND), U5.5 (~CE), U5.9 (GND), U5.25 (GND), U5.28 (~OE), U6.1 (OEa), U6.8 (GND), U6.15 (OEb), U7.8 (GND), U8.3 (GND), U11.3 (GND), U21.7 (GND)
unnamed: BT1.1 (+), D2.1
unnamed: C4.1, C7.1, D2.3, U3.11 (VDD), U3.33 (VDD), U4.11 (VDD), U4.33 (VDD)
unnamed: J10.5, U2.12
unnamed: J11.1, R2.2, U2.1
unnamed: J11.2, U2.2
unnamed: U1.19 (CE), U21.8
unnamed: U3.8 (~CE), U21.3
unnamed: U3.15 (~WE), U4.15 (~WE), U21.11
unnamed: U4.8 (~CE), U21.6
unnamed: U5.6 (I/O0), U6.6 (I0a), U7.15 (QA)
unnamed: U5.7 (I/O1), U6.5 (I1a), U7.1 (QB)
unnamed: U5.10 (I/O2), U6.4 (I2a), U7.2 (QC)
unnamed: U5.11 (I/O3), U6.3 (I3a), U7.3 (QD)
unnamed: U5.22 (I/O4), U6.10 (I0b), U7.4 (QE)
unnamed: U5.23 (I/O5), U6.11 (I1b), U7.5 (QF)
unnamed: U5.26 (I/O6), U6.12 (I2b), U7.6 (QG)
unnamed: U5.27 (I/O7), U6.13 (I3b), U7.7 (QH)
unnamed: U7.12 (RCLK), U8.4
unnamed: U11.4, U21.1
